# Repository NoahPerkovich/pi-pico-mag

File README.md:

# pi-pico-mag
Instrument prototyping to monitor electromagnetic  noise induced by power lines

This is a data aquisistion system intended to record the magnetic field induced by overhead or burried electric transmission lines. Basically an indirect current monitor or ampmeter.

## Disclaimer

There are still several issues to work out. The write to SD card protocol causes unwanted delays at random times during data sampling. The communication protocol using Xbee is not complete but I intend to use the radio to communicate with other aquisition systems in am manner that they share with eachother the times they intend to record data and syncronize. Command sequence with the ADS could likely be improved to both increase speed and accuracy. The low pass filter designed is for practice and demonstration only. In later versions i intend to use pre-build filter chips for anti-aliasing.

## Usage

### setting up the device and pico
The circuit can be built by following the circuit diagrams found in this repository. The pi pico needs to be flashed using the bootsell button on the pico and the flahs file found in this repo prior to uploading any code. Flahs file can of course be found online, it is the standard flash file for micropython pico.

### Test and Debug
Debugging the sensor and analog digital conversion is easiest when using a live reading. The notebook (read_sensor_live.ipynb) can be used as a serial monitor. You have to set the com port, and the components. This will read data if the pico has all of the following files:
- operate/helpers.py
- operate.sdcard.py
- tests/print_ADS/main.py

To test the GPS the pico should have the following files uploaded:
- operate/helpers.py
- operate.sdcard.py
- tests/print_GPS/main.py 
Monitor text through a serial monitor. Once the GPS has a valid signal it will print information. Verify accuracy

To test the sd card operations follow similar procedure as testing the GPS but with the file:
- tests/sd_file_io/main.py
The sd card must be formatted in FAT32. If it does not operate as expected check formatting on a pc then reinsert into device. 

the driver file for the sdcard breakout board via spi was found on a forum and is accessible via this link
https://github.com/micropython/micropython/files/13183364/sdcard.py.zip, and i was unable to recover the name of the author who created thisversion of the driver. Note this one works far better than the one on the official micropython-lib main branch

### Operate as a data aquisition tool
The sampling rate can be set in the operate/main.py file. Select desired sampling rate from the list found in operate/helpers.py. Those are the only options the ADS recognizes. This is a target rate, due to the fileio speed in the sd card and limited memory on the pico, the desired sampling rate will likely not be achieved if over 1000Hz. The size of the files can also be set. this is the number of samplies recorded continously before closing the file. The file naming convention can also be modified in main.py
The pico must have the following files uploaded:
- operate/helpers.py
- operate.sdcard.py
- operate/main.py

To ensure proper operation the device can be connected to a serial monitor. Inspect the text during initialization to ensure all parts are operating. Proper operation when not using gps for time syncronization should look like this:

Initializing ADS1256
Data rate set to 15000 SPS (DRATE value: 0xe0)
Current Data Rate Register Value: 0xe0
DRDY = 0
not using gps
Initializing SD board
SD card mounted.
measuring 1 component 30000 samples
New file created: /sd/30_nogps_x_1.bin
measuring 1 component 30000 samples
New file created: /sd/16_nogps_x_2.bin
Program terminated by stop.
SD card unmounted successfully.
end

There are 2 switches and 2 buttons in the design. 
- One switch enables the GPS. if using outdoors you can enable it and the sampling will automatically check the PPS signal and save a flag in the recorded times most significant bit when the pps goes hot. If using indoors, deisable gps otherwise the sensor will just wait for a valid gps signal before starting data aquisition.
- The other switch toggles between 1 and 2 component magnetic field measnurment. The device struggles to keep up with sampling rates over 500Hz in 2 component mode. This is becuase a command is sent to the ADS between each measnurment to switch to different MUX inputs. The switching takes time.
- A button between hte two switches is for stopping data aquisition. This should be used before powering down the instrument to allow the sd card to be unmounted.
- A button near the pico can be used to restart the entire initialization then data aquisition. When not connected to a pc for serial monitoring. you can interpret the lights on the board as indicators that the process is running correctly. If a light does not flicker on the sd card's board. This indicates that data is not being recorded. Restart with the button. When using gps, the blue LED should pulse every second. If gps is enabled and this is not occuring, restart with the button.

Files are saved in binary format with some basic metadata saved in plain text at the beginning of each file. The binary format for one samplie is:
- Pack data: [raw_data (3 bytes), combined_time (4 bytes)] for single component measurement
- Pack data: [raw_data_x (3 bytes), combined_time_x (4 bytes), raw_data_y (3 bytes), combined_time_y (4 bytes)] 
And the syncronization pulese is savd in the most significant bit in the combined_time or combine_time_x.

Basic file read and plotting can be done with the notebook (read_sensor_files.ipynb). Because the 2 component measurment is still onot optimized and likely requires an additional ADS for high rate sampling, the notebook currently only reads 3SI formated files which are the sinlge component files. Small modification can be made to read the 2 component files, however this is a work in progress.

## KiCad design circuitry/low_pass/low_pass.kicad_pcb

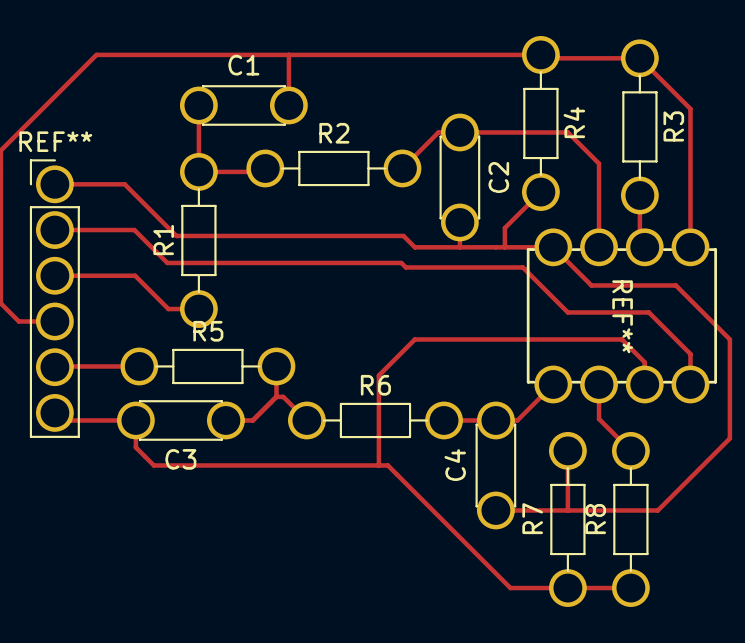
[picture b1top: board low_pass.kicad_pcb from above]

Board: 2 copper layers, 12 parts (0 on the bottom side), 7 nets.

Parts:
C1, C2, C3, C4: C_Disc_D4.3mm_W1.9mm_P5.00mm
R1, R2, R3, R4, R5, R6, R7, R8: R_Axial_DIN0204_L3.6mm_D1.6mm_P7.62mm_Horizontal

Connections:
GND: C2.2, C4.1, R4.2, R7.2
in1: C1.1, R1.1, R1.2, R2.1
in2: C3.1, R5.1, R5.2, R6.1
out1: C1.2, R3.1, R4.1
out2: C3.2, R7.1, R8.1
plus1: C2.1, R2.2
plus2: C4.2, R6.2

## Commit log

2024-12-04 setting up repo
    .not all things are in yet, not all things are complete
2024-12-06 cleaner repo
2024-12-06 update ignore
2024-12-06 added images of prototype
2024-12-06 ads test file and live reading in notebook
2024-12-06 better compartmentalized tests
2024-12-06 work on readme
2024-12-07 improve readme
2024-12-07 small edits
